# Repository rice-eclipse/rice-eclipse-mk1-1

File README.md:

# rice-eclipse-mk1-1
The official repository for mark 1.1 code and pcb schematics for the Rice Eclipse Rocketry Club at Rice University.

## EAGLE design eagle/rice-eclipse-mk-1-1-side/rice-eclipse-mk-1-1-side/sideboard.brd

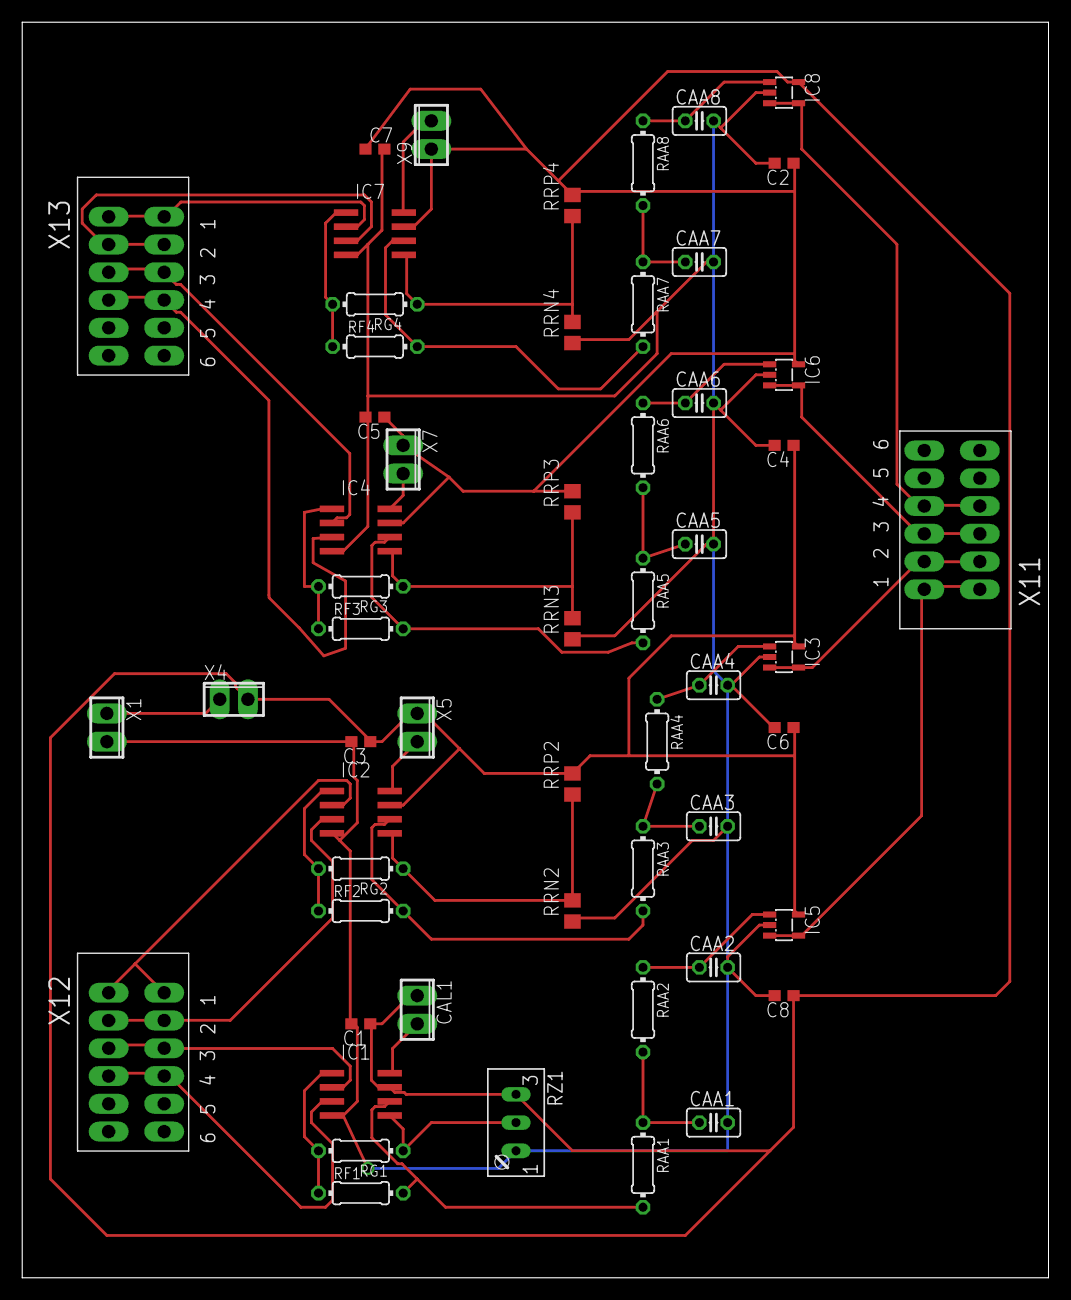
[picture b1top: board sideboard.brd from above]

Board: 2 copper layers, 92.4 x 113.0 mm, 56 parts (0 on the bottom side), 39 nets.

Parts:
C1, C3, C5, C7: 1UF; C0603
C2, C4, C6, C8: 10nF; C0603
CAA1, CAA2, CAA3, CAA4, CAA5, CAA6, CAA7, CAA8: C025-025X050
CAL1: 2POL254
IC1, IC2, IC4, IC7: MCP6N11R; SO-8
IC3, IC5, IC6, IC8: LMV321LICTRT; SOT23-5
RAA1, RAA2, RAA3, RAA4, RAA5, RAA6, RAA7, RAA8: 0204/7
RF1, RF2, RF3, RF4: 0204/7
RG1, RG2, RG3, RG4: 0204/7
RRN2, RRN3, RRN4: R0805
RRP2, RRP3, RRP4: R0805
RZ1: S64W
X1, X4, X5, X7, X9: 2POL254
X11, X12, X13: 1770924

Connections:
+3V3: C1.1, C2.1, C3.1, C4.1, C5.1, C6.1, C7.1, C8.1, CAL1.1, IC1.7, IC2.7, IC3.5, IC4.7, IC5.5, IC6.5, IC7.7, IC8.5, RRP2.2, RRP3.2, RRP4.2, RZ1.E, X4.2, X5.1, X7.1, X9.1
GND: C1.2, C2.2, C3.2, C4.2, C5.2, C6.2, C7.2, C8.2, CAA1.2, CAA2.2, CAA3.2, CAA4.2, CAA5.2, CAA6.2, CAA7.2, CAA8.2, IC1.4, IC2.4, IC3.2, IC4.4, IC5.2, IC6.2, IC7.4, IC8.2, RRN2.1, RRN3.1, RRN4.1, RZ1.A, X1.2
LC1_OUT: IC5.3, IC5.4, X11.P$1, X11.P$7
LC2_OUT: IC3.3, IC3.4, X11.P$2, X11.P$8
LC3_OUT: IC6.3, IC6.4, X11.P$3, X11.P$9
LC4_OUT1: IC8.3, IC8.4, X11.P$4, X11.P$10
unnamed: IC2.3, X12.P$2, X12.P$8
unnamed: IC2.2, X12.P$1, X12.P$7
unnamed: X1.1, X4.1
unnamed: IC1.6, RAA1.2, RF1.2
unnamed: CAL1.2, IC1.8
unnamed: CAA1.1, RAA1.1, RAA2.2
unnamed: IC1.1, RF1.1, RG1.2
unnamed: IC1.5, RG1.1, RZ1.S
unnamed: CAA2.1, IC5.1, RAA2.1
unnamed: IC1.2, X12.P$3, X12.P$9
unnamed: IC1.3, X12.P$4, X12.P$10
unnamed: IC2.8, X5.2
unnamed: IC2.6, RAA3.2, RF2.2
unnamed: IC2.1, RF2.1, RG2.2
unnamed: CAA3.1, RAA3.1, RAA4.2
unnamed: CAA4.1, IC3.1, RAA4.1
unnamed: IC2.5, RG2.1, RRN2.2, RRP2.1
unnamed: IC7.2, X13.P$1, X13.P$7
unnamed: IC7.3, X13.P$2, X13.P$8
unnamed: IC4.8, X7.2
unnamed: IC4.6, RAA5.2, RF3.2
unnamed: IC4.1, RF3.1, RG3.2
unnamed: CAA5.1, RAA5.1, RAA6.2
unnamed: CAA6.1, IC6.1, RAA6.1
unnamed: IC4.5, RG3.1, RRN3.2, RRP3.1
unnamed: IC4.3, X13.P$4, X13.P$10
unnamed: IC4.2, X13.P$3, X13.P$9
unnamed: IC7.8, X9.2
unnamed: IC7.6, RAA7.2, RF4.2
unnamed: IC7.1, RF4.1, RG4.2
unnamed: CAA7.1, RAA7.1, RAA8.2
unnamed: CAA8.1, IC8.1, RAA8.1
unnamed: IC7.5, RG4.1, RRN4.2, RRP4.1

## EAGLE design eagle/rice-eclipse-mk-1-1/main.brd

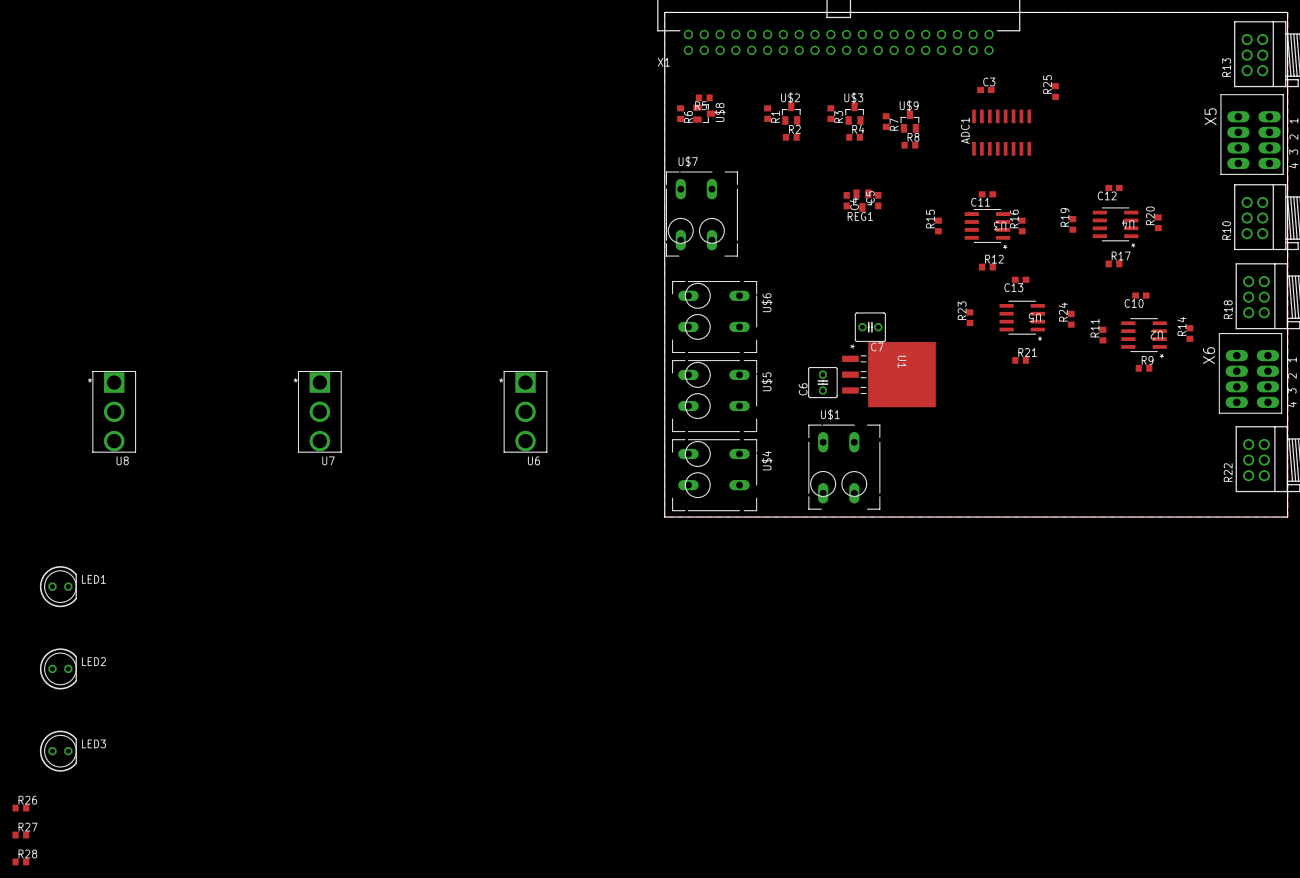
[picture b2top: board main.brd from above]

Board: 2 copper layers, 100.0 x 81.0 mm, 62 parts (0 on the bottom side), 52 nets, no tracks yet.

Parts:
ADC1: MCP3208SN; SO-16
C3, C5, C10, C11, C12, C13: 1UF; C0603
C4: 2.2UF; C0603
C6, C7: 10UF; C025-050X050
LED1, LED2, LED3: LED5MM
R1, R3, R5, R7: 10k; R0603
R2, R4, R6, R8: 500k; R0603
R9, R12, R17, R21: 33K; R0603
R10, R13, R18, R22: PTD902
R11, R14, R15, R16, R19, R20, R23, R24: 20K; R0603
R25: 500K; R0603
R26: 470; R0603
R27: 130; R0603
R28: 39; R0603
REG1: AP2210N-3.3TRG1; SOT23
U1: LM1084ISX-5.0/NOPB; TS3B
U2, U3, U4, U5: THS4531IDRD8-M; D8-M
U6, U7, U8: 1101M2S3CQE2
U$1, U$4, U$5, U$6, U$7: 1991095
U$2, U$3, U$8, U$9: 2N7000; SOT23
X1: 2540-5; PAK100/2500-5-40
X5, X6: 1770908

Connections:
+3V3: ADC1.15, ADC1.16, C3.1, C10.1, C11.1, C12.1, C13.1, LED3.A, R9.2, R12.2, R17.2, R21.2, R25.2, U2.3, U3.3, U4.3, U5.3
+3V3_DEBUG: C4.1, REG1.2, U8.2
+5V: LED2.A, U$5.A1, U$5.B1, X1.2
+5V_DEBUG: C7.1, U1.2, U1.4, U7.2
+10V: U$4.A2, U$4.B2
+12V: C5.1, C6.1, LED1.A, REG1.3, U1.3, U6.1, U$4.A1, U$4.B1
+12V_DEBUG: U6.2, U$1.A1, U$1.B1
ADC1_A0: ADC1.1, R14.2, U2.4
ADC1_A1: ADC1.2, R11.2, U2.5
ADC1_A2: ADC1.3, R16.2, U3.4
ADC1_A3: ADC1.4, R15.2, U3.5
ADC1_A4: ADC1.5, R20.2, U4.4
ADC1_A5: ADC1.6, R19.2, U4.5
ADC1_A6: ADC1.7, R24.2, U5.4
ADC1_A7: ADC1.8, R23.2, U5.5
ADC1_CS: R25.1, X1.22
CTRL_SOLENOID_1: R3.1, X1.11
CTRL_SOLENOID_2: R5.1, X1.13
CTRL_SOLENOID_3: R7.1, X1.15
GND: ADC1.9, ADC1.14, C3.2, C4.2, C5.2, C6.2, C7.2, C10.2, C11.2, C12.2, C13.2, R2.2, R4.2, R6.2, R8.2, R26.1, R27.2, R28.2, REG1.1, U1.1, U2.6, U3.6, U4.6, U5.6, U$1.A2, U$1.B2, U$2.2, U$3.2, U$5.A2, U$5.B2, U$8.2, U$9.2, X1.6
IGNITION_RELAY: R1.1, X1.16
LC_1_OUT+: R10.2-2, X5.P$1, X5.P$5
LC_1_OUT-: R10.1-2, X5.P$2, X5.P$6
LC_2_OUT+: R13.2-2, X5.P$3, X5.P$7
LC_2_OUT-: R13.1-2, X5.P$4, X5.P$8
LC_3_OUT+: R18.2-2, X6.P$1, X6.P$5
LC_3_OUT-: R18.1-2, X6.P$2, X6.P$6
LC_4_OUT+: R22.2-2, X6.P$3, X6.P$7
LC_4_OUT-: R22.1-2, X6.P$4, X6.P$8
unnamed: LED1.K, R26.2
unnamed: LED2.K, R27.1
unnamed: LED3.K, R28.1
unnamed: R1.2, R2.1, U$2.1
unnamed: R3.2, R4.1, U$3.1
unnamed: R5.2, R6.1, U$8.1
unnamed: R7.2, R8.1, U$9.1
unnamed: R9.1, U2.7
unnamed: R10.2-1, R11.1, U2.8
unnamed: R12.1, U3.7
unnamed: R13.2-1, R15.1, U3.8
unnamed: R10.1-1, R14.1, U2.1
unnamed: R13.1-1, R16.1, U3.1
unnamed: R17.1, U4.7
unnamed: R18.2-1, R19.1, U4.8
unnamed: R18.1-1, R20.1, U4.1
unnamed: R21.1, U5.7
unnamed: R22.2-1, R23.1, U5.8
unnamed: R22.1-1, R24.1, U5.1
RELAY_NEGATIVE: U$2.3, U$6.A1, U$6.B1
SOLENOID_1_NEGATIVE: U$3.3, U$6.A2, U$6.B2
SOLENOID_2_NEGATIVE: U$7.A1, U$7.B1, U$8.3
SOLENOID_3_NEGATIVE: U$7.A2, U$7.B2, U$9.3

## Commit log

2017-08-24 Added the eagle files and configured them for proper use. Added an empty software folder for now.
2017-08-25 Added a new library for our 3.3V regulator. Fixed library backups in eagle .gitignore.
2017-08-31 Added some new voltage regulators and used them. I also did something else, but I'm not sure what it was.
2017-09-02 Added a shorts library and some skeleton sheets in the schematic. Should provide a good environment for working on project.
2017-09-03 Added voltage regulator for -0.23v
2017-09-04 Added HelloWorld as a test
2017-09-04 edited wire
2017-09-07 Added a skeleton software setup.
    Includes a blink, and a dummy build that exit.
    Use cmake to just build them all and then run the one you want.
2017-09-07 Fixed the cmake file and project settings.
    CMakeLists is now changed so that the blink executable links
    the bcm2835 library. Also fixed the .gitignore so the build
    directory can be used properly to leave stuff from making a mess.
2017-09-07 Test commit for Tommy
2017-09-07 Test commit for Tommy 2
2017-09-07 Commit with .gitignore
2017-09-07 Fixed the gitignore to remove a ".lck" file.
2017-09-08 Added an echo_server test for the pi. Currently listens on port 1234.
    Some stuff not well set up, but that's to be expected.
2017-09-08 Added some debugging output to listener server.
2017-09-08 Added example spi code.
2017-09-09 Added a todo for echo_server.
2017-09-09 Added relay and solenoid driver stuff
2017-09-09 Added a new sheet for external connectors.
    Added raspberry PI GPIO to the sheet.
    Will probably add any outputs and inputs soon.
2017-09-09 Tweaked name of a wire.
2017-09-11 Added a bunch of libraries to eagle and added some stuff.
    Fixed double pins on phoenix 500 library item.
    Added signal connectors to eagle libs.
    Added op-amp to texas lib.
    Added some headers to listener.
2017-09-14 Added external connectors and basic load cell amp.
2017-09-14 Change license
    Original code was under MIT, but included several modified versions of GPL code, so it is necessary to change license. It is very unfortunate, but several releases before were under MIT with the wron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
2017-09-14 Added spi build target and fixed cpp compiler warning.
2017-09-17 Create mk1_gui
2017-09-21 Created a new build target for an adc abstraction.
2017-09-21 Added a 2 gang potentiometer for the gain tuning on load cell.
2017-09-24 Wrote two simple server examples that conform to a server interface.
    Neither example is useful as of yet, but they are verified to work with
    the gui from running on a linux computer (untested on rpi). Longterm
    the goal is to write an implementation of that interface that is better
    suited to asynchronous communication.
2017-09-25 Wrote jank code for adc_block.cpp. The read_item method is adapted from spi.cpp. The other methods are non-empty but might not be what we want.
2017-09-25 Create gui
2017-09-28 Thursday 9/28. Testing adc.cpp
2017-09-28 Thursday 9/28. Testing adc.cpp. Forgot some stuff in the previous push.
2017-09-28 Thursday 9/28. Testing adc.cpp. Testing on Pi
2017-09-29 Changed cstdint to stdint.h in adc_block.hpp
2017-09-30 Cleaned up the build file.
2017-09-30 Fixed the damn gitignore.
2017-09-30 finished load cell circuit copied it over
    ya
2017-10-01 Added a fancy echo server. The byte sending doesn't seem to be working right.
2017-10-01 Fixed adc_block.
2017-10-04 Removed some extraneous files.
2017-10-04 Merged in some code from the pi server branch.
    Also fixed a bug in the echo server.
2017-10-05 updated_gui_with_hostport_input
2017-10-05 Wrote some nice new stuff for the fancy server that works well.
2017-10-05 Made a threaded adc test thingy.
2017-10-06 Fixed some build stuff for the pi.
2017-10-06 Timestamp support for the adc test.
2017-10-07 Updated CmakeLists and build script for better builds.
    Fixed header in timestamps.
2017-10-07 rotated capacitors
2017-10-07 Added some debugging code.
2017-10-08 gui_withtimestamp-socke_server-added
2017-10-08 Added some unit testing to stuff.
2017-10-08 Slight improvements to unit tests.
2017-10-08 Determined the issue with the circular buffer giving garbage.
    Caused by padding of the adc_reading struct to a larger size.
    Best course of action is to leave it like this because it provides
    fine performance at little to no actual cost.
2017-10-08 Minor tweak.
2017-10-11 Cleaned up placement on the board. Router scares me.
2017-10-12 Added a new 4-pin signal connector. Also modified board.
2017-10-12 Added RPI GPIO connections.
2017-10-15 EAGLE stuff
    - changed 6 pin connectors to 4 pin for loadcells 1-4
    - deleted load cell 5 connector
    - added debugging slide switches
    - board rearranged
2017-10-15 Eagle Stuff
    changed 5v_debug to 5v
2017-10-21 Added test LEDs for schematic.
    LEDs allow for test of current.
2017-10-21 Deleted LEDS to resync board
2017-10-21 Added new libraries and fixed board annotation.
    LEDS had to be removed in the process. Will re-add in next
    version. I'm mostly just happy that the board is fixed.
2017-10-22 Added to the LEDs
2017-10-22 Cleaned up the board, added adcs, debug pins.
2017-10-22 Added more board parts.
2017-10-26 Added initial PT circuit guess and
    added some routes for power.
2017-10-26 Slightly increased size of power traces.
2017-10-29 Made a bunch of stuff.
2017-10-29 Added flyback diodes and moved stuff onto board.
2017-10-29 Added schottky diode.
2017-10-29 Added some stuff.
2017-10-29 Board is ready to route.
2017-10-29 Routed power traces. Autorouter starts next.
2017-10-30 Routed and messed with text.
2017-10-30 Routed and tried to gen board.
    Fixed cap sizes too.
2017-10-30 Removed all vias that were too small. Ready2Route.
2017-10-30 Moved all the stuff again.
2017-10-31 Resized board and ready to reroute.
2017-11-11 Some updates to circ buff usage.
    Fixed bug for fancy server operation.
    Next step is to completely reorganize the project layout in other branch.
2017-11-18 Moved a bunch of files around and cleaned up the server structure.
2017-11-19 Wrote a new server abstraction that works nicely.
    However there's a lot of boilerplate code and no documentation.
    Fixing that now.
2017-11-19 Added some minor documentation.
2017-11-19 Added sideboard.
2017-11-19 Added and routed.
2017-11-19 Rerouted with more stuff.
2017-11-28 Changed circular buffer to build with older version of C++
2017-11-28 Fixed code for board to pull GPIO 22 high, which is connected to the CS pin for a third ADC, which we would like to disable.
2017-11-30 Wrote a bunch of new networking code that is probably broken.
2017-11-30 Verified that the networking code is now much more robust.
2017-12-01 GUI code rewrite in progress. Hopefully easier for me to use. Currently the queue stuff is still really broken.
2017-12-01 GUI networking is yet again more robust. Still has no good way of signaling that we've lost connection or trying to reconnect, but that's a problem for another day.
2017-12-01 GUI networking somewhat broken when receiving messages. Will add some helpful debug logging and then I'll look into the issue.
2017-12-01 Good transitioning into more clean state. Still some kinks to solve.
2017-12-01 Fixed some stupid byte alignment bullshit.
2017-12-01 Things are going pretty well. A couple more steps to maybe get things working.
2017-12-01 Verified counter and plotting working well.
    Some major problem where it seems to print a value that's too large.
    That's something I'll investigate.
2017-12-01 Redrawing works nicely.
2017-12-01 Fixed network worker code to compile correctly.
2017-12-01 I think the reading is now correct pending a concurrency issue with the python gui where the animate method can't get a lock.
2017-12-01 Cleaned counter worker
    Fixed compiler error in main network worker
    Added extra include to pi so we can use offsetof.
    Fixed some major bugs with circular buffer.
2017-12-02 Fixed some timing issues.
2017-12-02 Made start of final setup + threaded adc test into new format.
    Took forever to fix compiler problems.
2017-12-02 Fixed some adc block errors.
    Verified the ADC looping code works.
2017-12-02 Changed some stuff.
2017-12-02 Wrote some simple output switching code.
2017-12-02 Modified main worker. Realized I had done stuff wrong.
2017-12-02 im dumb
2017-12-02 Added some stuff: logging in Plotter, buttons for calibrate/valve actuation/disconnect, Jeremy's nut button, and more plots.
2017-12-02 Cleaned things up and added some more of Jeremy's stuff. Going to sleep now.
2017-12-02 Fixed some initialization code.
2017-12-02 Starting some timing code that should work I hope.
2017-12-02 I think. I hope the ADC code will work and everything will be fine.
2017-12-02 I think it's all working now. Will test on PI.
2017-12-02 Fixed the timed ignition with hardcoded values. Please kill me.
2017-12-02 Bashing down a couple bugs in adc running code. Still in progress.
2017-12-02 Added some more stuff to fix issues.
2017-12-02 AFJKjkzdfjk;dgjaredgaadjkl
2017-12-02 Added handling for separate payloads. Need to change button locations.
2017-12-02 Changed unspecified things.
2017-12-03 Please work
2017-12-03 Fuck wq
2017-12-03 It's ugly and slow but data/graphing works. Deleting old values would be helpful.
2017-12-03 Fixed small but where logging wasn't happening. Not sure if format is correct. See previous commmit for larger issues that are still unsolved.
2017-12-03 Finalized code on gui. do not change please.
2017-12-03 Final gui.
2017-12-21 In the process of making the graphs look nicer and the code more readable. Taking a break to eat fried chicken.
2017-12-22 GUI is less ugly and code is shorter. Added a way to specify amount of data to graph.
2017-12-24 Removed some profanity and clarified a couple documentation pieces.
2017-12-26 In process of adding tabs. Graph updating speed is improved from before.
2017-12-28 Added some more buttons and cosmetic improvements. I'm disabling animation for now while I work on adding the ability to change graphs through the GUI.
2017-12-28 Changing graphs seems to work for random data, but there will probably be bugs when we try to test it with real data.
2017-12-30 Changed the backend queues into lists, which allows us to keep old data after reading it and index data directly. It makes the code cleaner, but performance might be affected. Added feature: ability 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
2017-12-30 Fixed a bug that affected axes autoscaling.
2018-01-02 Put some stuff in the logging tab.
2018-01-20 Removed some profanity and clarified a couple documentation pieces. Also added a start of a logger, but I doubt it works or even compiles.

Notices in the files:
parts and their libraries:
COPYRIGHT: Copyright (C) 2015 Accelerated Designs. All rights reserved
